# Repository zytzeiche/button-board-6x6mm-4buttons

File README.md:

# button-board-6x6mm-4buttons

External button board for buttons for Arduino or Raspberry Pi.

- Dimensions: 52 x 36 mm
- Mounting holes: M3 holes (3.2 mm), distance 36 and 20 mm
- Buttons: 6x6 mm tactile push buttons

This board can be used for Button pins, which are pulled high or pulled low. If the button pin is pulled low, solder a bridge to VCC for that button.

__Instructions__

- Solder a bridge on the back side of the board for every button. For a pin which is pulled low by default, solder the bridge to GND.

__More PCBs__

- [Button Board with 3 Buttons](https://github.com/zytzeiche/button-board-6x6mm-3buttons)

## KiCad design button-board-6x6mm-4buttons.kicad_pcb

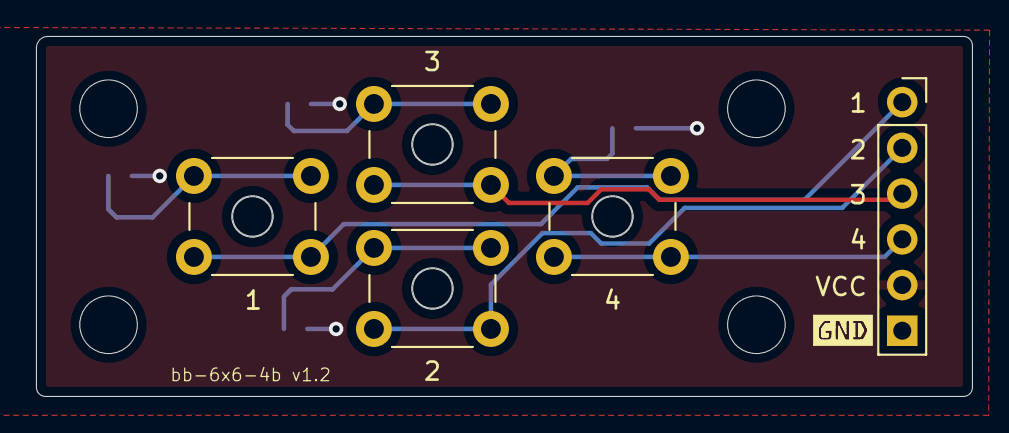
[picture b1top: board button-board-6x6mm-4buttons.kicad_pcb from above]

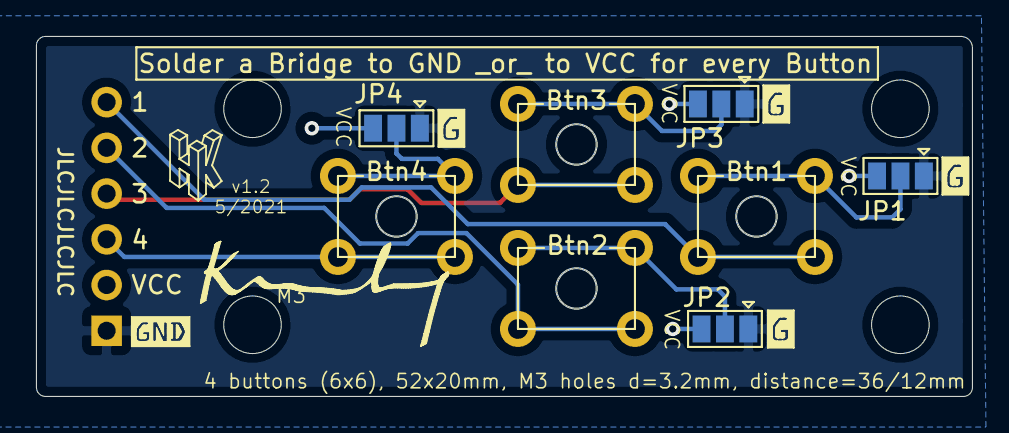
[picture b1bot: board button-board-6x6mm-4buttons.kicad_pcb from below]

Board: 2 copper layers, 52.0 x 20.0 mm, 17 parts (4 on the bottom side), 10 nets.

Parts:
H1, H5, H7, H8: MountingHole; MountingHole_3.2mm_M3
H2, H3, H4, H6: MountingHole; MountingHole_2.2mm_M2
J1: Conn_01x06_Male; PinSocket_1x06_P2.54mm_Vertical
JP1, JP2, JP3, JP4: Jumper_3_Open; SolderJumper-3_P1.3mm_Open_Pad1.0x1.5mm
SW1, SW2, SW3, SW4: SW_Push; SW_PUSH_6mm_H7.3mm

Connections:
GND: J1.6, JP1.1, JP2.1, JP3.1, JP4.1
unnamed: J1.1, SW1.2
unnamed: J1.2, SW2.2
unnamed: J1.3, SW3.2
unnamed: J1.4, SW4.2
unnamed: JP1.2, SW1.1
unnamed: JP2.2, SW2.1
unnamed: JP3.2, SW3.1
unnamed: JP4.2, SW4.1
VCC: J1.5, JP1.3, JP2.3, JP3.3, JP4.3

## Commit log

2021-05-22 Initial Version
2021-05-22 pdf updated
2021-05-22 readme with images of the pcb
2021-05-22 silkscreen minor update
2021-05-23 images
2021-05-23 added KiCads _autosave-button-board-6x6mm-4buttons.kicad_pcb files to gitignore
2021-05-23 added file
2021-05-23 update to v1r1
2021-06-10 doc update
2021-06-10 zip archive removed
2022-05-07 SilkScreen correction
2022-05-07 2 Footprints locked
